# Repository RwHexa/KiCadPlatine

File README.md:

# KiCadPlatine — Netzteil 230 V~ → +12 V, vollständig von einer KI entwickelt

Ein KiCad-8-Projekt für ein einfaches Linearnetzteil mit dem Festspannungsregler **7812**.
Das Besondere daran ist nicht die Schaltung — die steht in jedem Lehrbuch — sondern **wie
sie entstanden ist**: Der komplette Entwurf wurde von der KI **Claude** (Anthropic,
über Claude Code) erstellt. Vorgabe war ein einziges Bild.

---

## 🤖 Was die KI gemacht hat

**Alles zwischen Vorgabe und fertigen Produktionsdaten — in rund 55 Minuten:**

| Schritt | Ergebnis |
|---|---|
| Bibliotheken analysiert | Symbole und Footprints geprüft statt geraten |
| **Schaltplan** entworfen | 14 Bauteile, 8 Netze, `.kicad_sch` |
| **Bauteilwerte berechnet** | Trafo, Ladeelko, Sicherung, Verlustleistung |
| **Platine layoutet** | Bauteilplatzierung, Primär/Sekundär getrennt |
| **Vollständig geroutet** | 50 Leiterbahnsegmente, nur 2 Durchkontaktierungen |
| **Massefläche** angelegt | bewusst nur sekundärseitig |
| **Sicherheitsregel** definiert | eigene DRC-Regel: 6,4 mm Kriechstrecke |
| **Fehler gefunden und behoben** | u. a. zwei echte Kurzschlüsse |
| **Produktionsdaten** erzeugt | Gerber, Bohrdatei, Stückliste, PDFs |

**Was der Mensch beigetragen hat:** das Vorgabebild, zwei Entscheidungen
(Trafo auf der Platine statt extern, 0,5 A Ausgangsstrom) sowie Durchsicht und Freigabe.
Keine einzige Leiterbahn wurde von Hand gezogen.

Der Entwurf entstand **nicht durch Klicken in der KiCad-Oberfläche**, sondern über
Python-Generatorskripte (`kiutils`, `pcbnew`, `kicad-cli`). KiCad selbst diente als
Prüfinstanz. Das ganze Projekt lässt sich mit einem Befehl reproduzieren:

```bash
python build_all.py
```

## 📋 Die Vorgabe

Mehr als dieses Bild und der Satz *„möchte mit KiCad eine Platine gebaut haben mit
Festspannungsregler 7812 sowie in der Bilddatei beschrieben"* gab es nicht:

## ✅ Geprüfter Stand

| Prüfung | Ergebnis |
|---|---|
| ERC (Schaltplanprüfung) | **0 Verstöße** |
| DRC (Designregelprüfung) | **0 Verstöße**, 0 unverbundene Anschlüsse |
| Kriechstrecke Primär ↔ Sekundär | **≥ 6,4 mm**, per eigener Regel nachgerechnet |
| Platinengröße | **92,2 × 77,2 mm**, 2 Lagen, bedrahtet (THT) |

Die Prüfberichte [`erc.rpt`](Platine7812/erc.rpt) und [`drc.rpt`](Platine7812/drc.rpt)
liegen im Repository — der Stand ist also nachprüfbar, nicht nur behauptet.

Bewusst unter 100 × 100 mm: Unterhalb dieser Grenze fertigen die üblichen Anbieter
deutlich günstiger. Dafür wanderte die gesamte Sekundärseite unter den Trafo.

## 🔬 Was die KI beim Prüfen gefunden hat

Der interessanteste Teil des Projekts. KiCads Prüfwerkzeuge deckten Fehler auf, die im
Layout wie normale Linien aussehen:

- **Zwei echte Kurzschlüsse** — je eine Leiterbahn lief mitten durch ein fremdes Lötauge
  (Phase durch den Neutralleiter-Anschluss, Masse durch den Reglereingang).
- **Netzlose „Geisterpads"** — der mitgelieferte KiCad-Trafo-Footprint legt 12 Kupferpads
  an, benennt aber nur 4. Die übrigen 8 wären blanke Kupferinseln direkt neben 230 V~
  geworden. Daraus wurde ein eigener, sauberer 4-Pad-Footprint abgeleitet.
- **Zu enge Abstände bei Netzspannung** — die Netzklemme wurde daraufhin von 5,08 mm auf
  10 mm Raster getauscht.

## 💡 Zwei Werte, die von der Vorlage abweichen

Die KI hat nachgerechnet und zwei Angaben des Vorlagentexts bewusst geändert:

**Sekundärspannung 15 V~ statt 18 V~**

```
15 V~ → Scheitelwert 15 · √2                          = 21,2 V
        − 2 Diodenflussspannungen (2 · 0,7 V)         = 19,8 V
        − Brummspannung I·t/C = 0,5 A · 10 ms / 2200 µF = 2,3 V
        → am Reglereingang bleiben                    ≈ 17,5 V
```

Der 7812 braucht mindestens 14 V — 3,5 V Reserve bleiben. Die überschüssige Spannung
verheizt der Regler: mit 15 V~ sind das **3,3 W**, mit 18 V~ wären es **5,5 W** gewesen.

**Trafo 15 VA statt 10 VA** — bei Gleichrichtung mit Ladeelko fließt der Strom in kurzen
Spitzen; der Trafo-Effektivstrom ist rund 1,6…1,8 × der Gleichstrom. Für 0,5 A DC sind das
ca. 0,85 A. Ein 10-VA-Typ liefert bei 15 V nur 0,67 A und wäre überlastet.

## 📦 Inhalt

```
Platine7812/
  Platine7812.kicad_sch     Schaltplan
  Platine7812.kicad_pcb     Leiterplatte, fertig geroutet
  Platine7812.kicad_dru     eigene DRC-Regel (6,4 mm Isolation)
  Platine7812.pretty/       projekteigener Trafo-Footprint
  fertigung/                Gerber, Bohrdatei, ZIP, Stückliste, PDFs
  erc.rpt · drc.rpt         Prüfberichte
  README.md                 technische Doku mit Auslegungsrechnung

  build_all.py              erzeugt das komplette Projekt neu
  build_schematic.py        Schaltplan-Generator
  build_pcb.py              Platinen-Generator (Platzierung + Routing)
  make_trafo_footprint.py   eigener Trafo-Footprint
  setup_project.py          Netzklassen
  make_fabrication.py       Produktionsdateien

PlatineKi.md                Werkstattbericht über die Entstehung
```

Die technischen Details stehen in [`Platine7812/README.md`](Platine7812/README.md),
die Entstehungsgeschichte in [`PlatineKi.md`](PlatineKi.md).

## ⚠️ Sicherheitshinweis

> Die **Primärseite dieser Platine führt Netzspannung (230 V~)**. Nachbau, Inbetriebnahme
> und Messung nur durch entsprechend qualifizierte Personen, mit Trenntrafo und niemals bei
> offenem Gehäuse. Primär- und Sekundärseite sind galvanisch getrennt (SELV am Ausgang).

## 🔧 Vor einem Nachbau zu prüfen

1. **Trafo-Anschlussmaße** gegen das Datenblatt des tatsächlich beschafften 15-VA-Trafos
   abgleichen. Der Footprint ist vom generischen KiCad-Trafo 37 × 44 mm abgeleitet; nach
   oben sind nur 2,4 mm Luft zur Platinenkante.
2. **Kühlkörper** für U1 aussuchen (≤ 15 K/W). Die Fläche von 19 × 14 mm ist freigehalten.
   Ohne Kühlkörper schaltet der 7812 bei 3,3 W thermisch ab.

Das Projekt ist geprüft, aber **noch nicht als Hardware aufgebaut**.

## 📄 Lizenz

[MIT](LICENSE) — die Lizenz gilt für **alle Bestandteile** dieses Repositorys: die
Generatorskripte, die KiCad-Entwurfsdateien und die Produktionsdaten. Nachbauen,
verändern und weitergeben sind ausdrücklich erwünscht, auch kommerziell; der
Copyright-Hinweis muss erhalten bleiben.

Wie in der MIT-Lizenz festgehalten, erfolgt die Weitergabe **ohne jede Gewährleistung**.
Das ist hier mehr als eine Formalie: Die Platine führt Netzspannung und ist bislang
geprüft, aber nicht als Hardware aufgebaut. Wer sie nachbaut, trägt die Verantwortung
für die eigene Ausführung — siehe Sicherheitshinweis oben.

---

*KiCad 8.0.8 · kiutils / pcbnew / kicad-cli · Entwurf: Claude (Anthropic) via Claude Code · Rw*

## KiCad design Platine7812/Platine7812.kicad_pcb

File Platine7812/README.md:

# Platine7812 — einfaches Netzteil 230 V~ → +12 V DC

KiCad-8-Projekt nach dem Referenz-Schaltbild: Printtrafo **TR1** → Brücken­gleich­richter
aus **4 × 1N4007** → Siebung **C1/C2** → Festspannungsregler **LM7812** → **C3/C4** →
Ausgangsklemmen **JP1 (+12 V)** und **JP2 (0 V = GND)**.

> ⚠️ **LEBENSGEFAHR:** Die **Primärseite führt Netzspannung (230 V~)**. Primär- und
> Sekundärseite sind galvanisch getrennt (SELV am Ausgang). Aufbau, Inbetriebnahme und
> Messung nur durch qualifizierte Personen, Trenntrafo verwenden, Platine nie offen
> betreiben. Der 0-V-Anschluss wird beim Einbau ins Gehäuse mit dem Schutzkontakt verbunden.

## Stand

| Prüfung | Ergebnis |
|---|---|
| ERC (Schaltplan) | **0 Verstöße** |
| DRC (Leiterplatte) | **0 Verstöße**, **0 unverbundene Pads** |
| Kriechstrecke Primär↔Sekundär | **≥ 6,4 mm**, per eigener DRC-Regel nachgerechnet |
| Platinengröße | **92,2 × 77,2 mm**, 2 Lagen, THT |

Die Platine ist **vollständig geroutet** (50 Leiterbahnsegmente, 2 Durchkontaktierungen)
und hat eine gefüllte Massefläche auf der Rückseite — ausschließlich auf der
Sekundärseite, damit unter den netzspannungsführenden Bahnen kein Kupfer liegt.

## Stückliste

| Ref | Wert | Bauform / Footprint |
|---|---|---|
| TR1 | 230 V / 15 V, **15 VA** | Printtrafo, Körper 37 × 44 mm, 4 Pins |
| F1 | **T 160 mA / 250 V** | Feinsicherung 5 × 20 mm mit Printhalter, hochkant |
| J1 | Netzeingang L/N | Schraubklemme, **10 mm Raster** |
| D1–D4 | 1N4007 | DO-41, liegend, Raster 7,62 mm |
| C1 | 2200 µF / 35 V | Elko radial, Ø 16 mm, Raster 7,5 mm |
| C2 | 100 nF / 100 V | Folie, Raster 5 mm |
| U1 | **LM7812** | TO-220 stehend, **Kühlkörper erforderlich** |
| C3 | 100 nF / 50 V | Folie, Raster 5 mm |
| C4 | 100 µF / 25 V | Elko radial, Ø 10 mm, Raster 5 mm |
| JP1 / JP2 | +12 V / 0 V | je 1 Stift, Raster 2,54 mm |

## Auslegung — warum diese Werte

**Sekundärspannung 15 V~ (nicht 18 V~).** Der Text zum Referenzbild nennt 18 V als
Beispiel. 15 V reichen aber und halbieren fast die Verlustwärme:

```
15 V~ → Scheitelwert      15 · √2        = 21,2 V
        − 2 Diodenflussspannungen (2 · 0,7 V) = 19,8 V
        − Brummspannung  ΔU = I·t/C = 0,5 A · 10 ms / 2200 µF = 2,3 V
        → Minimum am Reglereingang            ≈ 17,5 V
```

Der 7812 braucht mindestens 14 V am Eingang (12 V + 2 V Dropout) — **3,5 V Reserve**.
Verlustleistung am Regler: `(18,6 V − 12 V) · 0,5 A ≈ 3,3 W`.
Mit 18 V~ wären es **5,5 W** gewesen.

**Kühlkörper ist Pflicht.** Bei 3,3 W und 40 °C Umgebung wird ein Kühlkörper mit
**≤ 15 K/W** gebraucht (Sperrschicht bleibt dann bei rund 105 °C). Auf der Platine ist
dafür eine Fläche von **19 × 14 mm** hinter U1 freigehalten und auf der Lage `Dwgs.User`
markiert. Ohne Kühlkörper schaltet der 7812 thermisch ab.

**Trafo 15 VA, nicht 10 VA.** Bei Gleichrichtung mit Ladeelko fließt der Strom in kurzen
Spitzen; der Trafo-Effektivstrom ist rund **1,6…1,8 × der Gleichstrom**. Für 0,5 A DC sind
das ca. 0,85 A — ein 10-VA-Typ liefert bei 15 V nur 0,67 A und wäre überlastet.
15 VA / 15 V = 1,0 A reicht mit Reserve.

**Sicherung.** Primär-Nennstrom `15 VA / 230 V = 65 mA`, träge Sicherung mit etwa dem
doppelten Wert → **T 160 mA**.

## Aufbau der Leiterplatte

**Primärseite oben** (y < 86 mm): J1 → F1 → TR1-Primärwicklung.
**Sekundärseite unten** (y > 90 mm): Brücke → C1/C2 → U1 → C3/C4 → JP1/JP2.
Dazwischen liegt die **Isolationsbarriere**; sie ist auf `Dwgs.User` eingezeichnet und
wird bauartbedingt nur vom Trafo selbst überbrückt (Pin-Reihenabstand 25,4 mm).

**Kreuzungsfreie Brückenanordnung.** D1 und D4 sind um 180° gedreht. Dadurch liegen die
beiden Kathoden (VRAW) innen nebeneinander und die beiden GND-Anoden ebenfalls:

```
AC1 --|<|-- VRAW   VRAW --|<|-- AC2     obere Reihe (D1 gedreht, D2)
AC1 --|<|-- GND    GND  --|<|-- AC2     untere Reihe (D3, D4 gedreht)
```

Die Brücke selbst braucht damit keine einzige Kreuzung. Nur VRAW muss die AC2-Bahn
queren — das erledigen zwei Durchkontaktierungen im freien Korridor zwischen den
Diodenreihen. GND läuft komplett auf der Rückseite und kann deshalb nichts kreuzen.

## Dateien

| Datei | Inhalt |
|---|---|
| `Platine7812.kicad_sch` | Schaltplan |
| `Platine7812.kicad_pcb` | Leiterplatte, geroutet |
| `Platine7812.kicad_pro` | Projektdatei inkl. Netzklassen |
| `Platine7812.kicad_dru` | **eigene DRC-Regel: 6,4 mm Primär ↔ Sekundär** |
| `Platine7812.net` | Netzliste (aus dem Schaltplan erzeugt) |
| `Platine7812.pretty/` | projekteigener Trafo-Footprint |
| `fertigung/` | Gerber, Bohrdateien, ZIP, Stückliste, PDFs |
| `erc.rpt`, `drc.rpt` | Prüfberichte |

### Generatorskripte

Das Projekt wird **vollständig aus Skripten erzeugt**; die Netzliste ist die einzige
Quelle der Wahrheit für die Leiterplatte (kein manueller Netzlisten-Import nötig).

```bash
python build_all.py
```

Das durchläuft der Reihe nach:

| Schritt | Skript | Ergebnis |
|---|---|---|
| 1 | `make_trafo_footprint.py` | Trafo-Footprint + `fp-lib-table` |
| 2 | `build_schematic.py` | `.kicad_sch` |
| 3 | `kicad-cli sch erc` | `erc.rpt` |
| 4 | `kicad-cli sch export netlist` | `.net` |
| 5 | `build_pcb.py` | `.kicad_pcb` (platziert, geroutet, Zone gefüllt) |
| 6 | `setup_project.py` | Netzklassen in `.kicad_pro` |
| 7 | `kicad-cli pcb drc` | `drc.rpt` |

Fertigungsdaten danach mit:

```bash
python make_fabrication.py
```

## Stolpersteine, die hier gelöst sind

1. **`LM7812_TO220` hat keine eigenen Pins** — das Symbol erbt sie per `extends` von
   `LM7805_TO220`. Wird es unverändert eingebettet, zeichnet Eeschema ein leeres Kästchen.
   `build_schematic.py` klopft es flach und schreibt die Unit-Namen um.
2. **Der KiCad-Trafo-Footprint hat Geisterpads.** `Transformer_THT:Transformer_37x44` legt
   12 Kupferpads an, nummeriert aber nur 4. Die 8 netzlosen Pads wären blanke Kupferinseln
   neben 230 V~. `make_trafo_footprint.py` leitet einen sauberen 4-Pad-Footprint ab.
3. **`kicad-cli` überschreibt die `.kicad_pro`** und wirft dabei eigene Netzklassen weg.
   Deshalb läuft `setup_project.py` immer **als letzter Schritt**.
4. **`ZONE_FILLER` stürzt** auf einem frisch erzeugten Board ab (Segfault). Auf einem
   *geladenen* Board mit `BuildConnectivity()` läuft er durch — `build_pcb.py` macht
   deshalb den Umweg Speichern → Laden → Füllen → Speichern. Ohne das bliebe die
   Massefläche in den Gerber-Dateien leer.
5. **Bohrdateien werden nicht mitgeplottet.** `export gerbers` liefert keine `.drl`;
   `make_fabrication.py` ruft `export drill` separat auf und bricht ab, wenn die
   Bohrdatei fehlt — ein ZIP ohne `.drl` ist beim Fertiger unbrauchbar.

## Vor dem Bestellen bitte prüfen

1. **Trafo-Footprint gegen das Datenblatt abgleichen.** Der Footprint ist vom generischen
   KiCad-Trafo 37 × 44 mm abgeleitet: Primärpads bei x = 0 / 20,32 mm, Sekundärpads bei
   x = ±5,08 mm, Reihenabstand 25,4 mm. **Rastermaß und Pinbelegung des tatsächlich
   beschafften Trafos prüfen** und notfalls in `make_trafo_footprint.py` anpassen.
2. **Kühlkörper aussuchen** (≤ 15 K/W) und prüfen, ob er in die freigehaltenen
   19 × 14 mm passt.
3. **Elko-Bauhöhen** gegen das geplante Gehäuse prüfen (C1 ist Ø 16 mm).
4. Die **Sicherung sitzt nur in der Phase (L)**. Für allpolige Trennung gehört ein
   zweipoliger Schalter vor die Platine.

---
*RwTec · 2026 · erstellt mit Claude Code aus dem Referenz-Schaltbild.*

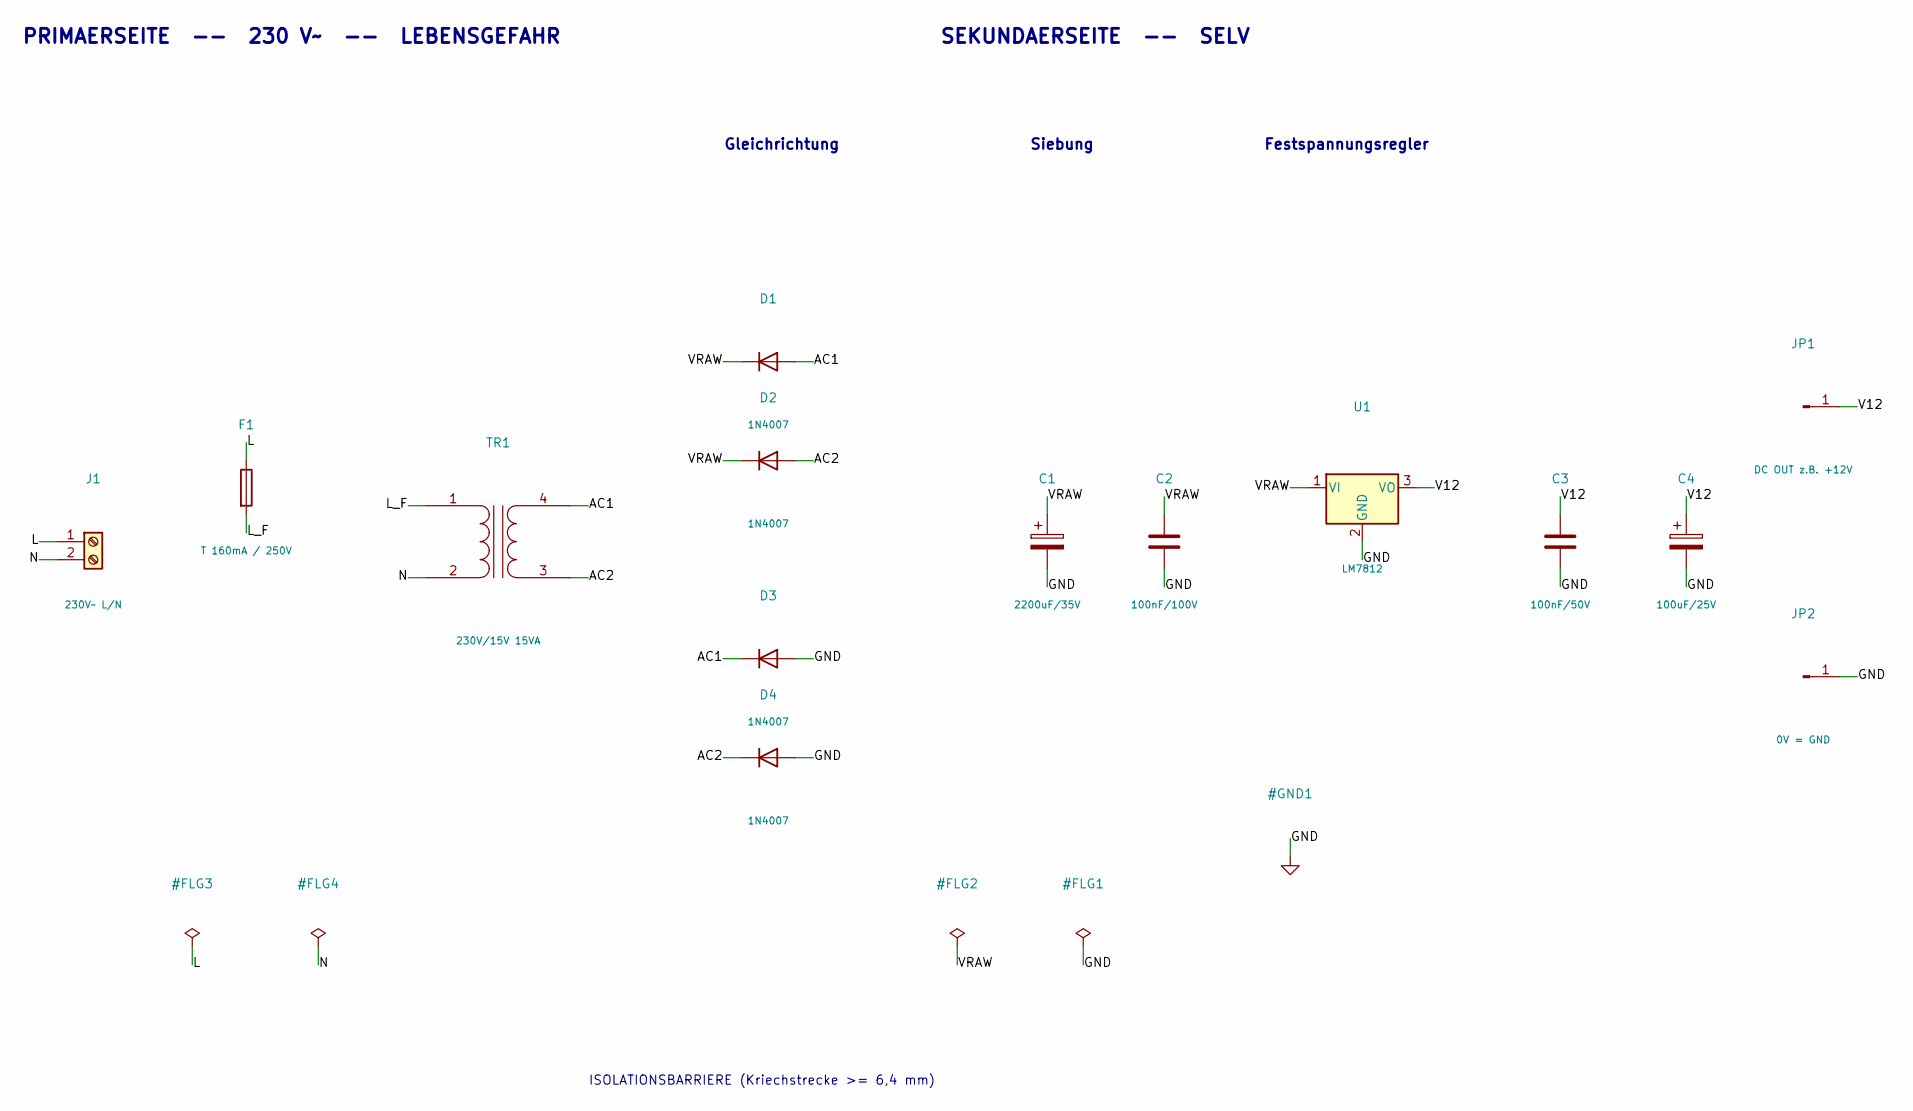
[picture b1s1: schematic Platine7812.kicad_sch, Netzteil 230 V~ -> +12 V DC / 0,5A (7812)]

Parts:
C1: 2200uF/35V; CP_Radial_D16.0mm_P7.50mm
C2: 100nF/100V; C_Rect_L7.0mm_W2.5mm_P5.00mm
C3: 100nF/50V; C_Rect_L7.0mm_W2.5mm_P5.00mm
C4: 100uF/25V; CP_Radial_D10.0mm_P5.00mm
D1, D2, D3, D4: 1N4007; D_DO-41_SOD81_P7.62mm_Horizontal
F1: T 160mA / 250V; Fuseholder_Clip-5x20mm_Littelfuse_111_Inline_P20.00x5.00mm_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
J1: 230V~ L/N; TerminalBlock_RND_205-00023_1x02_P10.00mm_Horizontal
JP1: DC OUT z.B. +12V; PinHeader_1x01_P2.54mm_Vertical
JP2: 0V = GND; PinHeader_1x01_P2.54mm_Vertical
TR1: 230V/15V 15VA; Trafo_Print_15VA_4pin
U1: LM7812; TO-220-3_Vertical

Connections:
/AC1: D1.2 (A), D3.1 (K), TR1.4 (SB)
/AC2: D2.2 (A), D4.1 (K), TR1.3 (SA)
/L: F1.1, J1.1
/L_F: F1.2, TR1.1 (AA)
/N: J1.2, TR1.2 (AB)
/V12: C3.1, C4.1, JP1.1, U1.3 (VO)
/VRAW: C1.1, C2.1, D1.1 (K), D2.1 (K), U1.1 (VI)
GND: C1.2, C2.2, C3.2, C4.2, D3.2 (A), D4.2 (A), JP2.1, U1.2 (GND)

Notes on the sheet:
PRIMAERSEITE -- 230 V~ -- LEBENSGEFAHR
Siebung
Festspannungsregler
ISOLATIONSBARRIERE (Kriechstrecke >= 6,4 mm)
SEKUNDAERSEITE -- SELV
Gleichrichtung

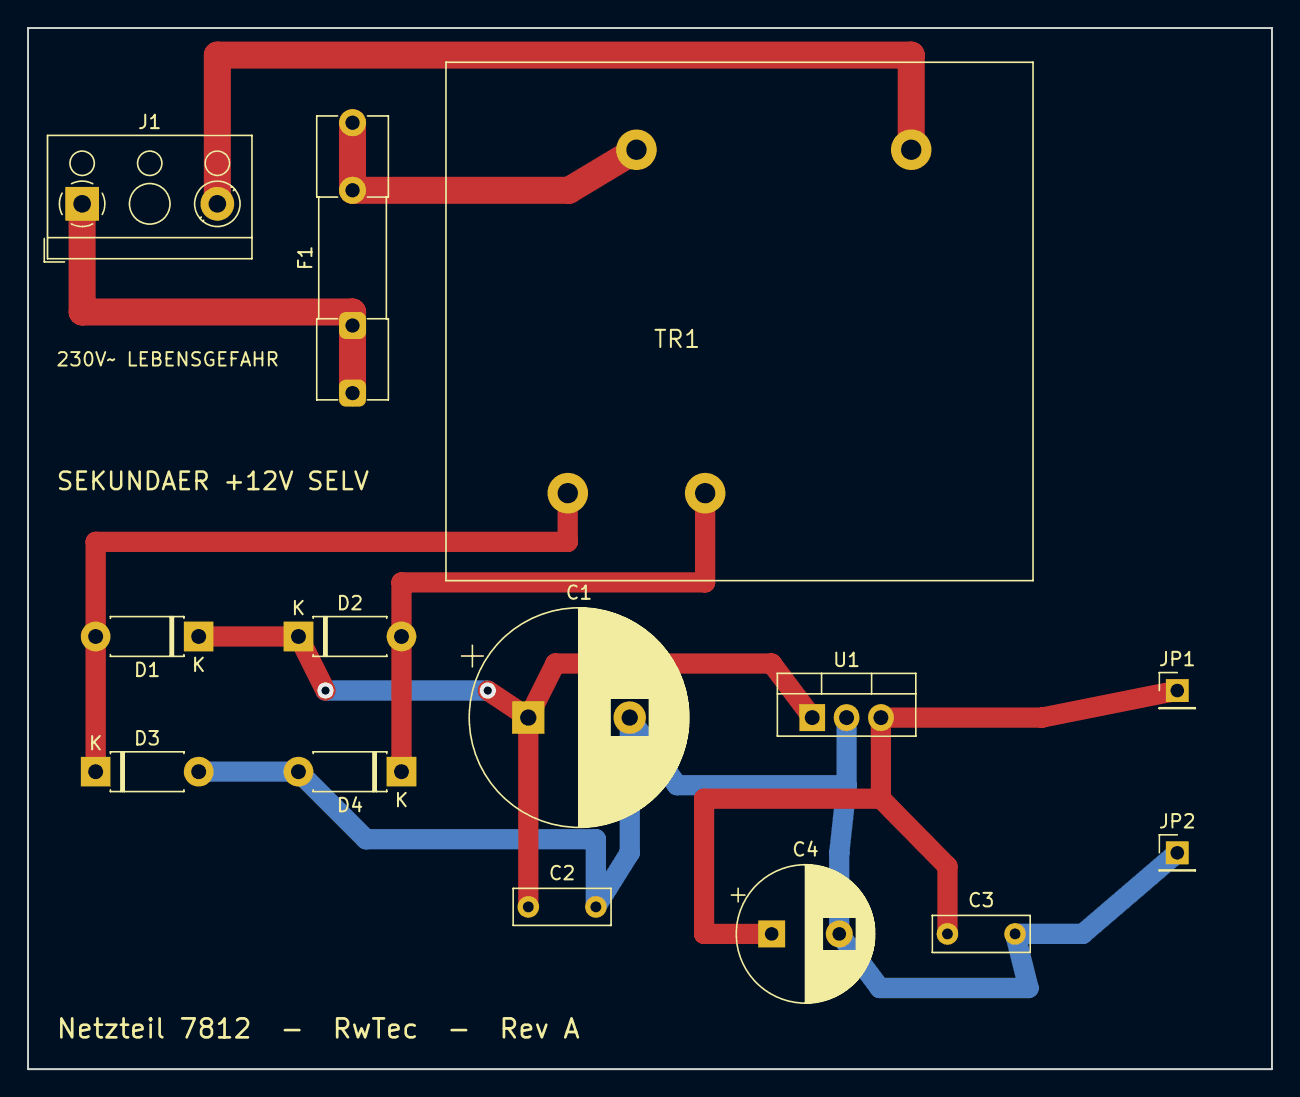
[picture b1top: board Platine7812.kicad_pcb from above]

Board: 2 copper layers, 92.0 x 77.0 mm, 14 parts (0 on the bottom side), 8 nets.
